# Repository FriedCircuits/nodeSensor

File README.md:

# nodeSensor
MQTT Sensor Node - Reed/Temp/Humidity/Light and La Crosse Gateway 

[Blog](http://www.mobilewill.us/2016/08/living-room-node-upgrade.html)

License: All source code and designs are released under 

Creative Commons By ShareAlike 

CC BY-SA

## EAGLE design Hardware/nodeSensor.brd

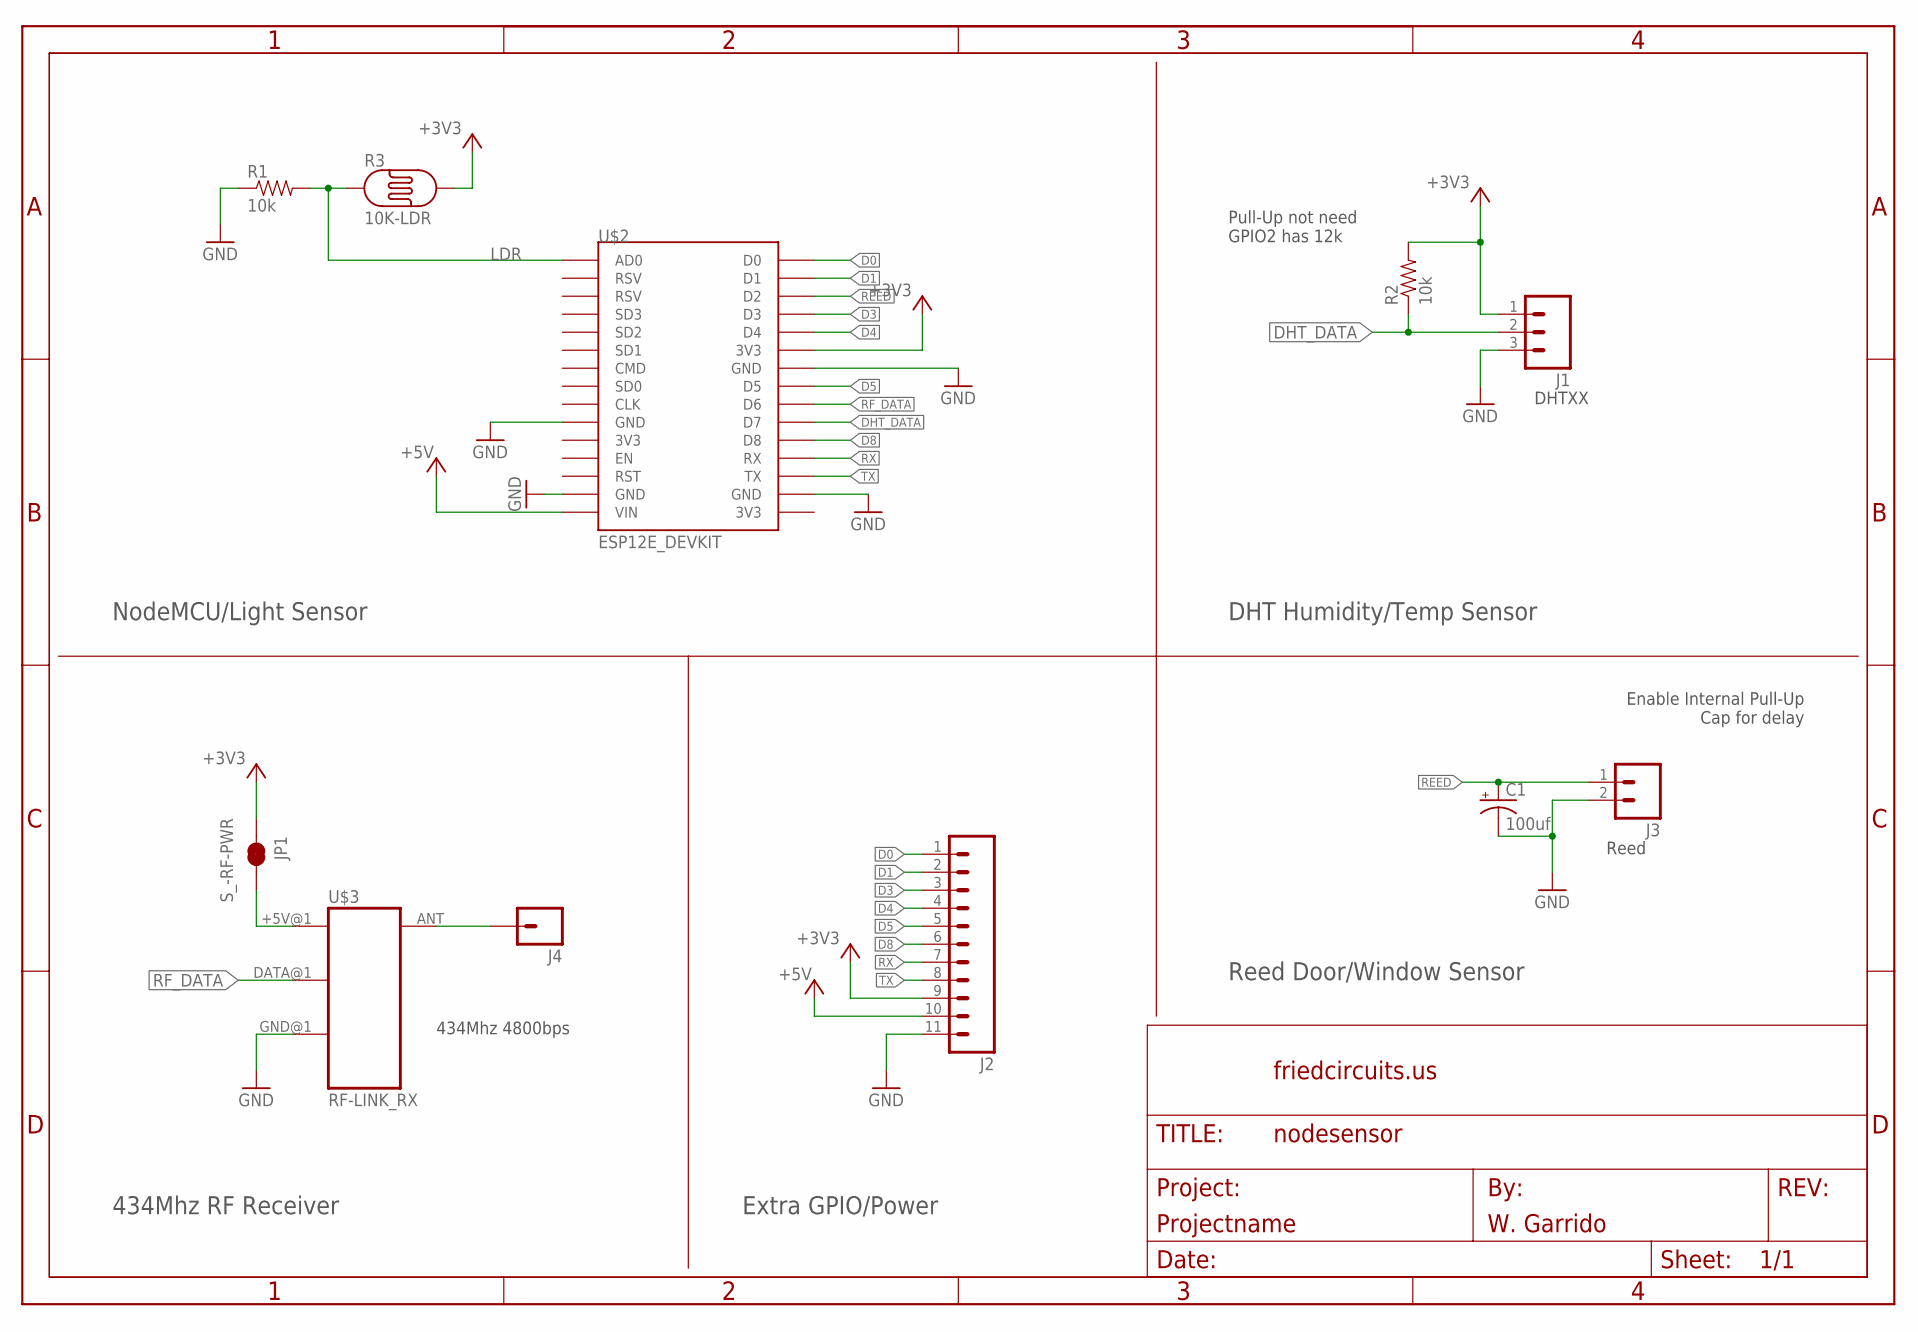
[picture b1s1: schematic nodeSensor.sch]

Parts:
C1: 100uf; CPOL-RADIAL-1000UF-25V
J1: M03LOCK; 1X03_LOCK
J2: M11LOCK; 1X11_LOCK
J3: M02LOCK; 1X02_LOCK
J4: M01PTH_LONGPAD; 1X01_LONGPAD
JP1: S_-RF-PWR; PAD-JUMPER-2-NC_BY_TRACE_YES_SILK
R1, R2: 10k; AXIAL-0.3-KIT
R3: 10K-LDR; PHOTOCELL
U$1: FRAME_DINA4_L; FC_CREDIT
U$2: ESP12E_DEVKIT
U$3: RF-LINK_RX

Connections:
+3V3: J1.1, J2.9, JP1.1, R2.P$2 (2), R3.2, U$2.3V3@1 (3V3)
+5V: J2.10, U$2.VIN
D0: J2.1, U$2.D0
D1: J2.2, U$2.D1
D3: J2.3, U$2.D3
D4: J2.4, U$2.D4
D5: J2.5, U$2.D5
D8: J2.6, U$2.D8
DHT_DATA: J1.2, R2.P$1 (1), U$2.D7
GND: C1.2 (-), J1.3, J2.11, J3.2, R1.P$1 (1), U$2.GND@0 (GND), U$2.GND@1 (GND), U$2.GND@2 (GND), U$2.GND@3 (GND), U$3.GND@1 (GND)
LDR: R1.P$2 (2), R3.1, U$2.AD0
unnamed: J4.1, U$3.ANT
unnamed: JP1.2, U$3.+5V@1 (+5V)
REED: C1.1 (+), J3.1, U$2.D2
RF_DATA: U$2.D6, U$3.DATA@1 (DATA)
RX: J2.7, U$2.RX
TX: J2.8, U$2.TX

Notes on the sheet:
DHTXX
Reed
434Mhz 4800bps
NodeMCU/Light Sensor
DHT Humidity/Temp Sensor
Reed Door/Window Sensor
Extra GPIO/Power
434Mhz RF Receiver
Enable Internal Pull-Up Cap for delay
Pull-Up not need GPIO2 has 12k

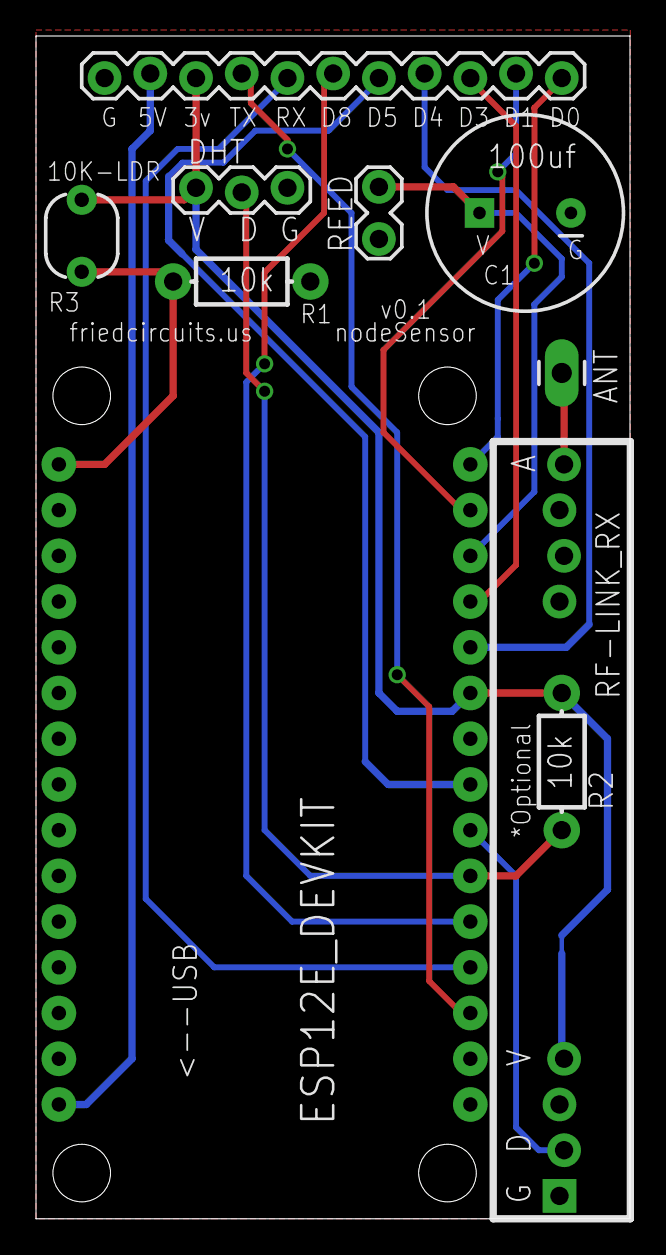
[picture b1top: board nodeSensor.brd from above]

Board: 2 copper layers, 33.0 x 65.7 mm, 12 parts (1 on the bottom side), 17 nets.

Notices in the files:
parts and their libraries:
SparkFun-Connectors: Licensing: Creative Commons ShareAlike 4.0 International - https://creativecommons.org/licenses/by-sa/4.0
